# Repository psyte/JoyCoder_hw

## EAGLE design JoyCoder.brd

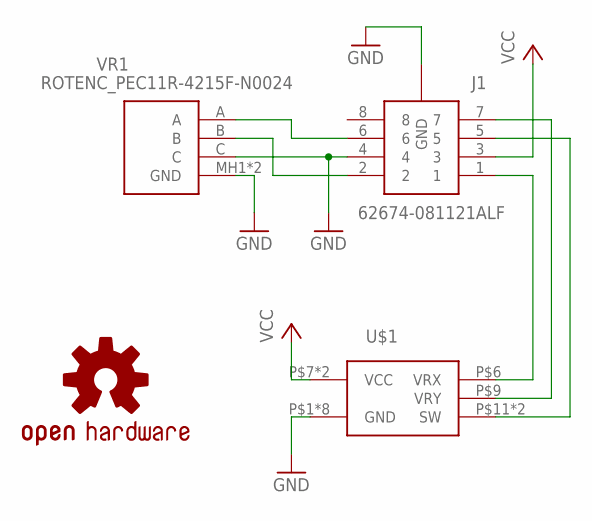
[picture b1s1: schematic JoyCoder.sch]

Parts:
J1: 62674-081121ALF; FCI_62674-081121ALF
LOGO1: OSHW-LOGOS; OSHW-LOGO-S
U$1: JOYSTICK; JOYSTICK_PS2
VR1: ROTENC_PEC11R-4215F-N0024

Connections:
GND: J1.4, J1.9 (GND), J1.10 (GND), J1.11 (GND), J1.12 (GND), U$1.P$1 (GND), U$1.P$2 (GND), U$1.P$3 (GND), U$1.P$4 (GND), U$1.P$5 (GND), U$1.P$8 (GND), U$1.P$13 (GND), U$1.P$14 (GND), VR1.C, VR1.MH1 (GND), VR1.MH2 (GND)
unnamed: J1.6, VR1.A
unnamed: J1.2, VR1.B
unnamed: J1.5, U$1.P$11 (SW), U$1.P$12 (SW)
unnamed: J1.7, U$1.P$9 (VRY)
unnamed: J1.1, U$1.P$6 (VRX)
VCC: J1.3, U$1.P$7 (VCC), U$1.P$10 (VCC)

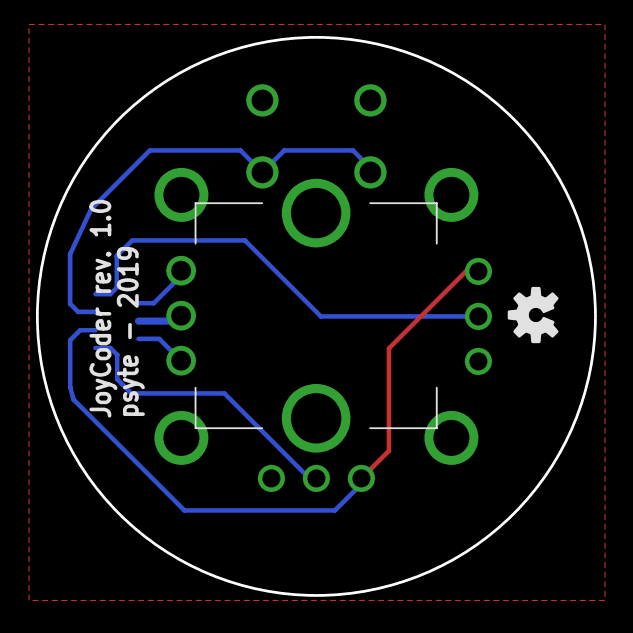
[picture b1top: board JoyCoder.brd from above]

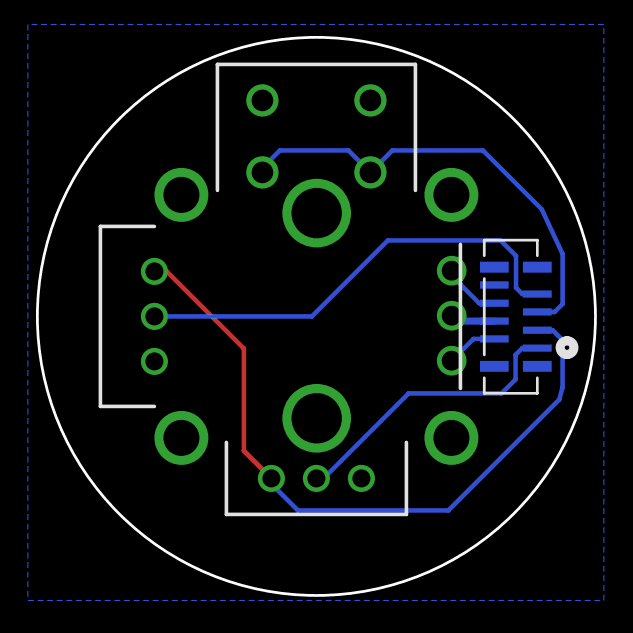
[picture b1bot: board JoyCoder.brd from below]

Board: 2 copper layers, 31.0 x 31.0 mm, 4 parts (2 on the bottom side), 7 nets.

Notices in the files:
parts and their libraries:
SparkFun-Aesthetics: Licensing: Creative Commons ShareAlike 4.0 International - https://creativecommons.org/licenses/by-sa/4.0
